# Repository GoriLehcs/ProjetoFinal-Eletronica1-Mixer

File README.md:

# Projeto Final — Eletrônica 1 (ES238, UFPE): Mixer

Mixer com MOSFET: somador inversor → MOSFET em fonte comum operando na lei quadrática → passa-baixa MFB (15,3 kHz) → passa-alta Sallen-Key (5,1 kHz). Com portadora de 10 kHz e modulante de 1 kHz, a saída é um sinal AM com bandas laterais em 9 e 11 kHz (índice de modulação ≈ 0,34 na simulação).

## Estrutura

| Pasta | Conteúdo |
| --- | --- |
| `KicadProjetoFinal/` | Projeto do KiCad: esquemático, configuração do simulador ngspice e placa de face única |
| `KicadProjetoFinal/Mixer.pretty/` | Biblioteca de footprints do projeto, com ilhas ampliadas para fresagem (registrada em `fp-lib-table`) |
| `KicadProjetoFinal/modelos/` | Modelos SPICE usados na simulação: IRF640N (Infineon) e TL084 (TI, cópia adaptada para o ngspice com invólucro quádruplo de 14 pinos) |
| `CompontentesExtrasSpice/` | Outros modelos e originais dos fabricantes: TL084 e LM324 (TI), OP07 (TI); `lm324_kicad.lib` é a cópia adaptada do LM324 |
| `Testes/` | Dados exportados do simulador (CSV com `;` como separador e `,` como decimal) |
| `docs/` | Enunciado do projeto |

## Abrir e simular

1. Abrir `KicadProjetoFinal/KicadProjetoFinal.kicad_pro` no KiCad 10 (o esquemático e a placa estão no formato do KiCad 10).
2. Os modelos usados ficam em `KicadProjetoFinal/modelos/` e são referenciados por caminho relativo à pasta do projeto (`modelos/...`), então o projeto funciona em qualquer computador.
3. Simulador: análise transitória de 5 ms com passo de 0,5 µs. Com o TL084, o ponto de operação DC converge e a simulação já começa em regime permanente.

## Valores atuais

Numeração após a reanotação de 23/11/2026. A configuração elétrica é a do teste 9; a única mudança é que R7 = 21,1 kΩ passou a ser 20 kΩ fixo + trimpot de 2 kΩ (RV2), ajustado na simulação para 1,1 kΩ.

| Componente | Valor | Função |
| --- | --- | --- |
| R1, R2 | 100 kΩ | Entradas do somador (portadora e voz) |
| R3 | 1,2 kΩ | Realimentação do somador (ganho −0,012) |
| R4 | 220 Ω | Isolamento da carga capacitiva da porta |
| C3 | 220 nF | Acoplamento da porta |
| R5, R6 + RV2 | 100 kΩ, 20 kΩ + 2 kΩ (≈ 1,1 kΩ) | Polarização da porta (VG ≈ −7,818 V, VOV ≈ 58 mV) |
| Q1 | IRF640N | Elemento não linear |
| R7 | 330 Ω | Dreno |
| R8, R9, R10, C6, C7 | 47 kΩ, 11 kΩ, 3 kΩ, 3,3 nF, 1 nF | Passa-baixa MFB |
| C9, C10, R11, R12 | 2,2 nF, 2,2 nF, 10 kΩ, 20 kΩ | Passa-alta Sallen-Key |
| U1 | TL084 | A: somador, B: passa-baixa, C: passa-alta, D: sem uso (seguidor) |
| RV1 | 100 kΩ | Nível da voz (divisor entre o microfone e R2) |
| U2, C5, C8 | L7805, 330 nF, 100 nF | 5 V para o módulo de microfone MAX4466 |
| C1, C2, C4 | 100 nF | Desacoplamento: +12 V e −12 V junto ao TL084; +12 V junto a R7 |
| J1 / J2 / J3 / J4 | KF301 2 vias / barra 1×3 / KF301 3 vias / KF301 2 vias | Portadora / microfone (VCC, GND, OUT) / alimentação (+12 V, GND, −12 V) / saída |
| Alimentação | ±12 V | |

## Placa (face única, fresagem CNC)

- Placa de 90 × 62 mm, cobre só na face inferior (B.Cu), com quatro furos M3 de 3,2 mm nos cantos.
- Regras de projeto: trilha de 0,8 mm (sinal) e 1,2 mm (alimentação), isolação de 0,5 mm, 1 mm de distância até a borda.
- Footprints da biblioteca `Mixer`: ilhas de 2,2 a 3,0 mm; nos componentes com passo de 2,54 mm as ilhas são ovais, alongadas na direção perpendicular à fileira.
- Roteamento feito com o Freerouting a partir de `KicadProjetoFinal_1face.dsn` (só a camada B.Cu; GND deixado para o plano de cobre). `KicadProjetoFinal.dsn` é a exportação original do KiCad.
- GND por plano de cobre na face inferior, com ligação sólida dos pads (sem alívio térmico, para não deixar pontes estreitas na fresagem).
- **Um jumper de fio** (trilha em F.Cu entre dois furos de GND, perto de J3): liga ao plano a ilha do pino de GND de J3, cercada pelas trilhas de +12 V e −12 V.
- DRC (`DRC.rpt`): nenhum erro, nenhum pad desconectado; restam só avisos de serigrafia, que a fresagem não usa.
- Na montagem, os bornes devem ficar com a entrada do fio voltada para a borda da placa.

## Registro dos testes

Os testes usam a numeração anterior à reanotação (por exemplo, R7 = 21,1 kΩ e R8 = 330 Ω no dreno).

| Arquivo | Configuração | Resultado principal |
| --- | --- | --- |
| `teste.csv` | LM324, polarização original, C1 = 2,2 µF | OP não convergiu; porta partiu de ≈ −4 V (Q1 em triodo) |
| `teste2.csv` | C1 = 220 nF, 10 ms | Estabilização com τ ≈ 4 ms; Q1 atravessando o limiar |
| `teste3.csv` | C1 = 220 nF, 30 ms | Regime permanente: Q1 cortado com o modelo da Infineon, sem mistura |
| `teste4.csv` | R3 = 1 kΩ, dreno = 330 Ω, R7 = 21,1 kΩ | Primeira mistura (9 e 11 kHz no dreno); efeito Miller identificado |
| `teste5.csv` | U1 trocado para TL084 | OP converge; terra virtual melhor; sem oscilação |
| `teste6.csv` | TL084, porta e dreno exportados | Perda de sinal na porta (Miller) confirmada em regime permanente |
| `teste7.csv` | R3 = 1,2 kΩ, saída exportada | AM completo na saída: 751 mV (10 kHz), 132 e 123 mV (9 e 11 kHz) |
| `teste7img.png` | — | Captura do simulador do teste 7 |
| `teste8.csv` | R7 = 21,2 kΩ (VOV ≈ 74 mV) | Bandas laterais caíram ≈ 30% pela realimentação via capacitância porta-dreno |
| `teste9.csv` | R4 (pull-down) retirado, R7 = 21,1 kΩ, V2 com polaridade corrigida | Configuração atual; resultado idêntico ao do teste 7 |

## Observações

- Os modelos SPICE são de seus fabricantes (Texas Instruments, Infineon) e seguem as licenças originais.
- A explicação detalhada do circuito e os relatórios de andamento estão em documentos separados do Claude.

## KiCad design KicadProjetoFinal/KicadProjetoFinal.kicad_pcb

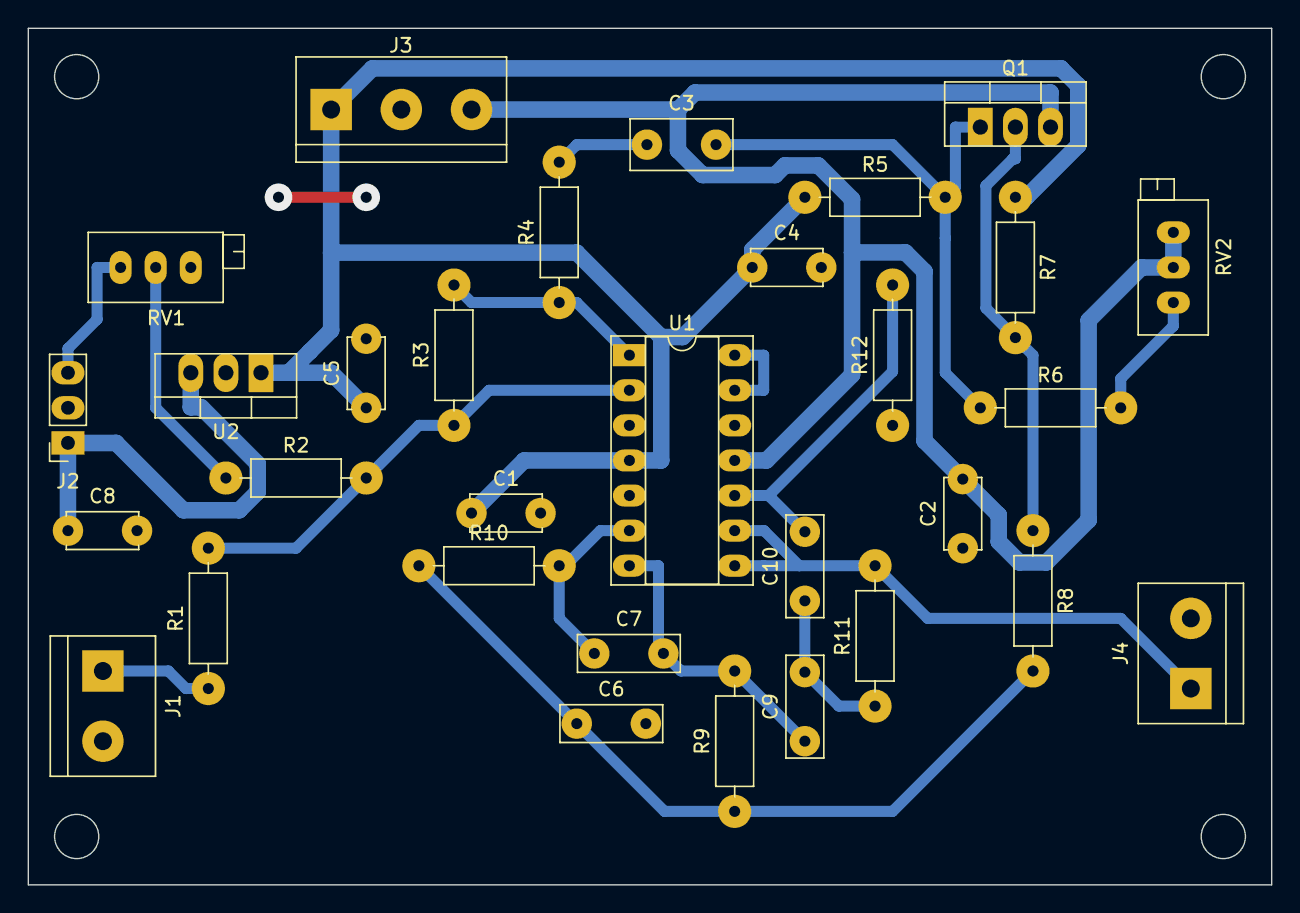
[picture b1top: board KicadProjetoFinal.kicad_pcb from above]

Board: 2 copper layers, 90.0 x 62.0 mm, 31 parts (0 on the bottom side), 20 nets.

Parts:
C1, C2, C4, C8: 100n; C_Disc_D5.0mm_W2.5mm_P5.00mm
C3: 220n; C_Rect_L7.2mm_W3.5mm_P5.00mm_FKS2_FKP2_MKS2_MKP2
C5: 330n; C_Disc_D5.0mm_W2.5mm_P5.00mm
C6: 3.3n; C_Rect_L7.2mm_W2.5mm_P5.00mm_FKS2_FKP2_MKS2_MKP2
C7: 1n; C_Rect_L7.2mm_W2.5mm_P5.00mm_FKS2_FKP2_MKS2_MKP2
C9, C10: 2.2n; C_Rect_L7.2mm_W2.5mm_P5.00mm_FKS2_FKP2_MKS2_MKP2
J1: Entrada portadora; KF301-2P_P5.08mm
J2: Microfone MAX4466; PinSocket_1x03_P2.54mm_Vertical
J3: Alimentação ±12 V; KF301-3P_P5.08mm
J4: Saída; KF301-2P_P5.08mm
Q1: IRF640N; TO-220-3_Vertical
R1, R2, R5: 100k; R_Axial_DIN0207_L6.3mm_D2.5mm_P10.16mm_Horizontal
R3: 1.2k; R_Axial_DIN0207_L6.3mm_D2.5mm_P10.16mm_Horizontal
R4: 220; R_Axial_DIN0207_L6.3mm_D2.5mm_P10.16mm_Horizontal
R6, R12: 20k; R_Axial_DIN0207_L6.3mm_D2.5mm_P10.16mm_Horizontal
R7: 330; R_Axial_DIN0207_L6.3mm_D2.5mm_P10.16mm_Horizontal
R8: 47k; R_Axial_DIN0207_L6.3mm_D2.5mm_P10.16mm_Horizontal
R9: 11k; R_Axial_DIN0207_L6.3mm_D2.5mm_P10.16mm_Horizontal
R10: 3k; R_Axial_DIN0207_L6.3mm_D2.5mm_P10.16mm_Horizontal
R11: 10k; R_Axial_DIN0207_L6.3mm_D2.5mm_P10.16mm_Horizontal
RV1: 100k; Potentiometer_Bourns_3296X_Horizontal
RV2: 2k; Potentiometer_Bourns_3296X_Horizontal
U1: TL084CN; DIP-14_W7.62mm_Socket
U2: L7805; TO-220-3_Vertical

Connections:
+5V: C8.1, J2.1, U2.3 (OUT)
+VDC: C1.1, C4.1, C5.1, J3.1, R5.1, R7.1, U1.4 (V+), U2.1 (IN)
-VDC: C2.2, J3.3, Q1.3 (S), RV2.2, RV2.3, U1.11 (V-)
GND: C1.2, C2.1, C4.2, C5.2, C6.2, C8.2, J1.2, J2.2, J3.2, J4.2, R12.1, RV1.3, U1.3 (+), U1.5 (+), U1.12 (+), U2.2 (GND)
unnamed: C3.1, R4.2
unnamed: C6.1, R8.2, R9.1, R10.1
unnamed: C7.2, C9.1, R9.2, U1.7
unnamed: C9.2, C10.1, R11.1
unnamed: J1.1, R1.1
unnamed: J2.3, RV1.1
unnamed: Q1.2 (D), R7.2, R8.1
unnamed: C3.2, Q1.1 (G), R5.2, R6.1
unnamed: R2.1, RV1.2
unnamed: R6.2, RV2.1
unnamed: R1.2, R2.2, R3.1, U1.2 (-)
unnamed: C7.1, R10.2, U1.6 (-)
unnamed: C10.2, R12.2, U1.10 (+)
unnamed: U1.13 (-), U1.14
saida: J4.1, R11.2, U1.8, U1.9 (-)
soma: R3.2, R4.1, U1.1
